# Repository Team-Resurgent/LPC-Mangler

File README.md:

# LPC Mangler
 
A WIP/Concept Mod for original xbox. Designed by Members from Team Resurgent.
It intercepts the LPC commands between the chipset and an LPC flash chip, rewriting the command and address bits so you can use larger, later chips that don't normally reside at the same addresses as typical LPC flash chips used in simpler mods like the Aladdin , and does so while adding as few extra clock cycles as possible to the transaction

Would love for the community to contribute & complete the design

Currently supports upto 4MB Flashes. Also has ability for serial output etc.

Requires Lframe to be implemented to work with higher rev xbox possibly.

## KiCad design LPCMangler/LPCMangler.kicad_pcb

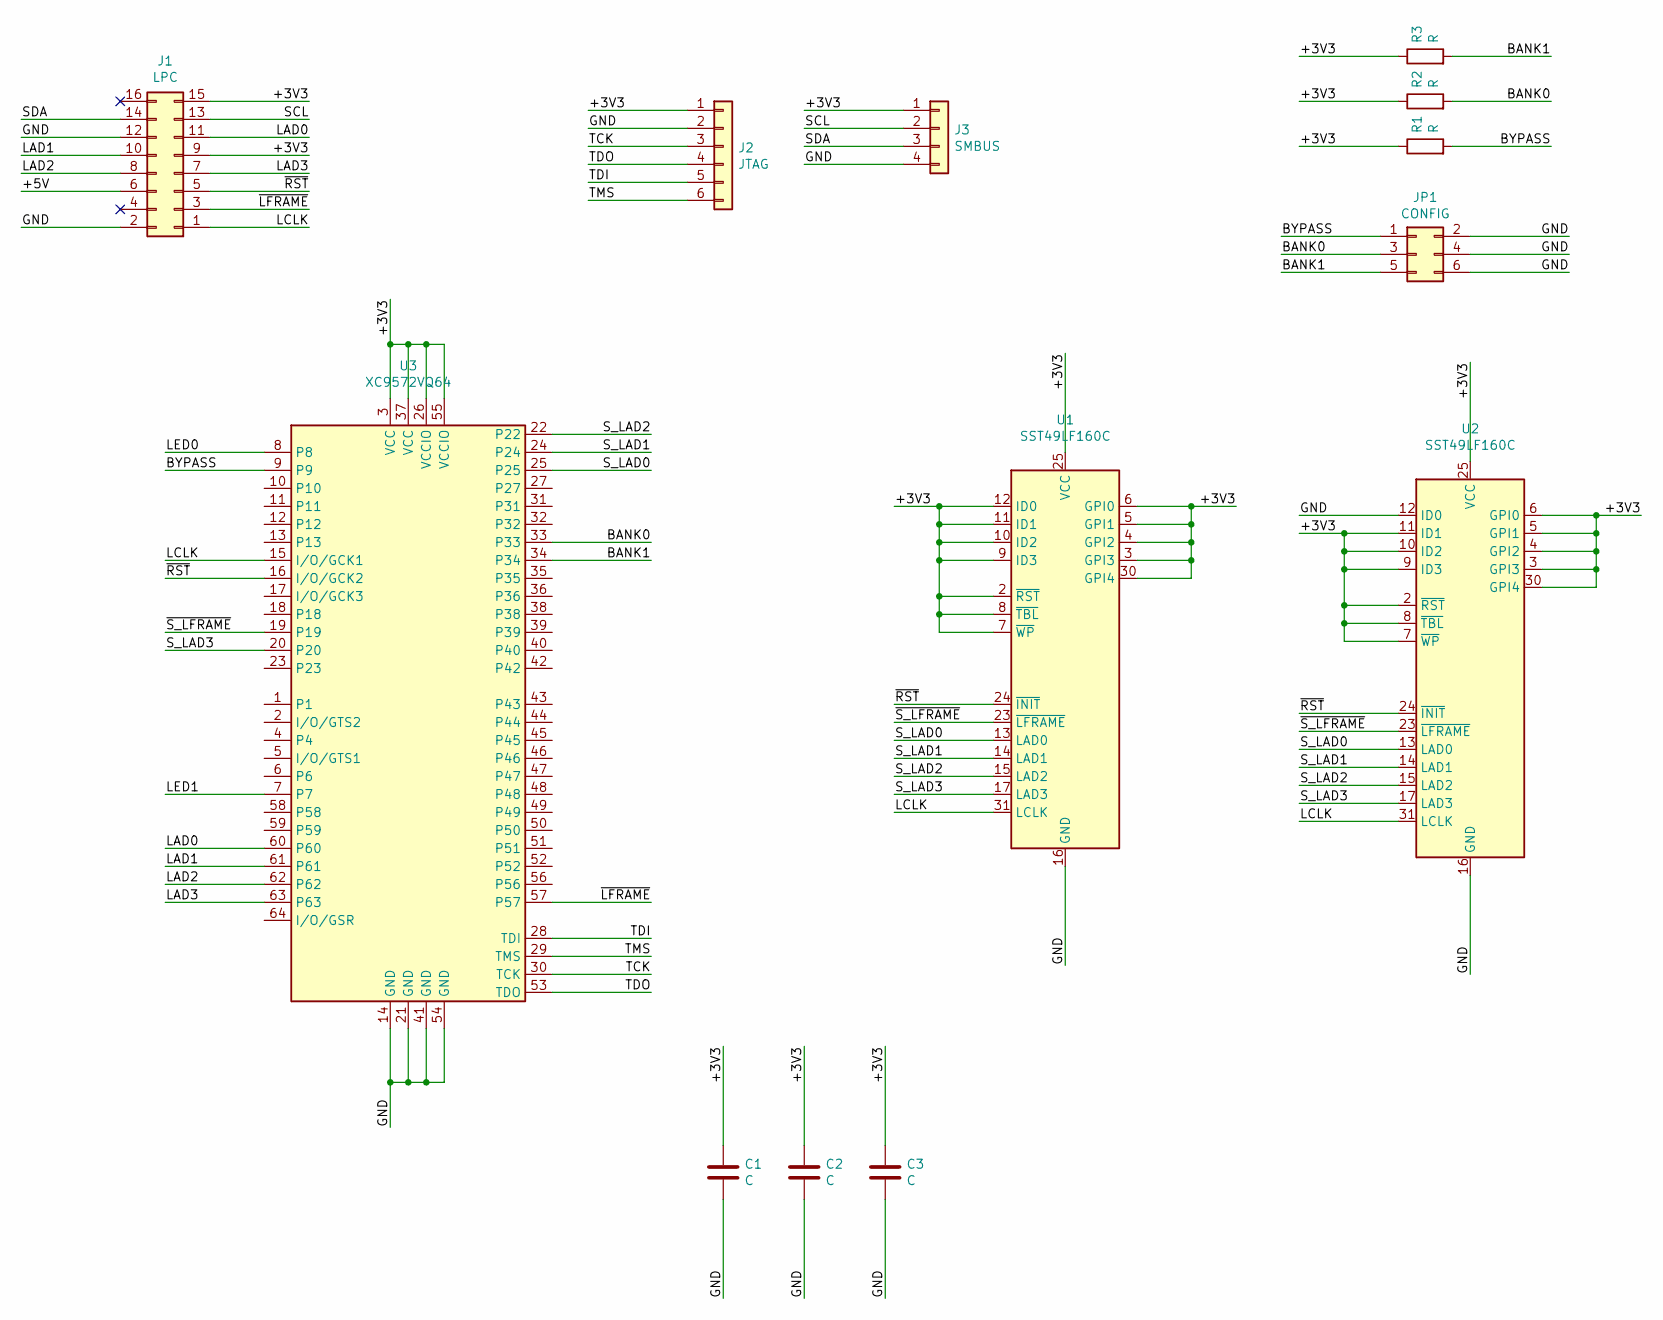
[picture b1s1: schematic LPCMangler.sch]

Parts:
C1, C2, C3: C; C_0603_1608Metric_Pad1.08x0.95mm_HandSolder
J1: LPC; PinSocket_2x08_P2.54mm_Vertical
J2: JTAG; PinHeader_1x06_P2.54mm_Vertical
J3: SMBUS; PinHeader_1x04_P2.54mm_Vertical
JP1: CONFIG; PinHeader_2x03_P2.54mm_Vertical
R1, R2, R3: R; R_0603_1608Metric_Pad0.98x0.95mm_HandSolder
U1, U2: SST49LF160C; PLCC-32_THT-Socket
U3: XC9572VQ64; TQFP-64_10x10mm_P0.5mm

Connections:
/+3V3: C1.1, C2.1, C3.1, J1.9, J1.15, J2.1, J3.1, R1.1, R2.1, R3.1, U1.2 (~RST), U1.3 (GPI3), U1.4 (GPI2), U1.5 (GPI1), U1.6 (GPI0), U1.7 (~WP), U1.8 (~TBL), U1.9 (ID3), U1.10 (ID2), U1.11 (ID1), U1.12 (ID0), U1.25 (VCC), U1.30 (GPI4), U2.2 (~RST), U2.3 (GPI3), U2.4 (GPI2), U2.5 (GPI1), U2.6 (GPI0), U2.7 (~WP), U2.8 (~TBL), U2.9 (ID3), U2.10 (ID2), U2.11 (ID1), U2.25 (VCC), U2.30 (GPI4), U3.3 (VCC), U3.26 (VCCIO), U3.37 (VCC), U3.55 (VCCIO)
/+5V: J1.6
/BANK0: JP1.3, R2.2, U3.33
/BANK1: JP1.5, R3.2, U3.34
/BYPASS: JP1.1, R1.2, U3.9
/GND: C1.2, C2.2, C3.2, J1.2, J1.12, J2.2, J3.4, JP1.2, JP1.4, JP1.6, U1.16 (GND), U2.12 (ID0), U2.16 (GND), U3.14 (GND), U3.21 (GND), U3.41 (GND), U3.54 (GND)
/LAD0: J1.11, U3.60
/LAD1: J1.10, U3.61
/LAD2: J1.8, U3.62
/LAD3: J1.7, U3.63
/LCLK: J1.1, U1.31 (LCLK), U2.31 (LCLK), U3.15 (I/O/GCK1)
/LED0: U3.8
/LED1: U3.7
/SCL: J1.13, J3.2
/SDA: J1.14, J3.3
/S_LAD0: U1.13 (LAD0), U2.13 (LAD0), U3.25
/S_LAD1: U1.14 (LAD1), U2.14 (LAD1), U3.24
/S_LAD2: U1.15 (LAD2), U2.15 (LAD2), U3.22
/S_LAD3: U1.17 (LAD3), U2.17 (LAD3), U3.20
/TCK: J2.3, U3.30 (TCK)
/TDI: J2.5, U3.28 (TDI)
/TDO: J2.4, U3.53 (TDO)
/TMS: J2.6, U3.29 (TMS)
/~LFRAME: J1.3, U3.57
/~RST: J1.5, U1.24 (~INIT), U2.24 (~INIT), U3.16 (I/O/GCK2)
/~S_LFRAME: U1.23 (~LFRAME), U2.23 (~LFRAME), U3.19

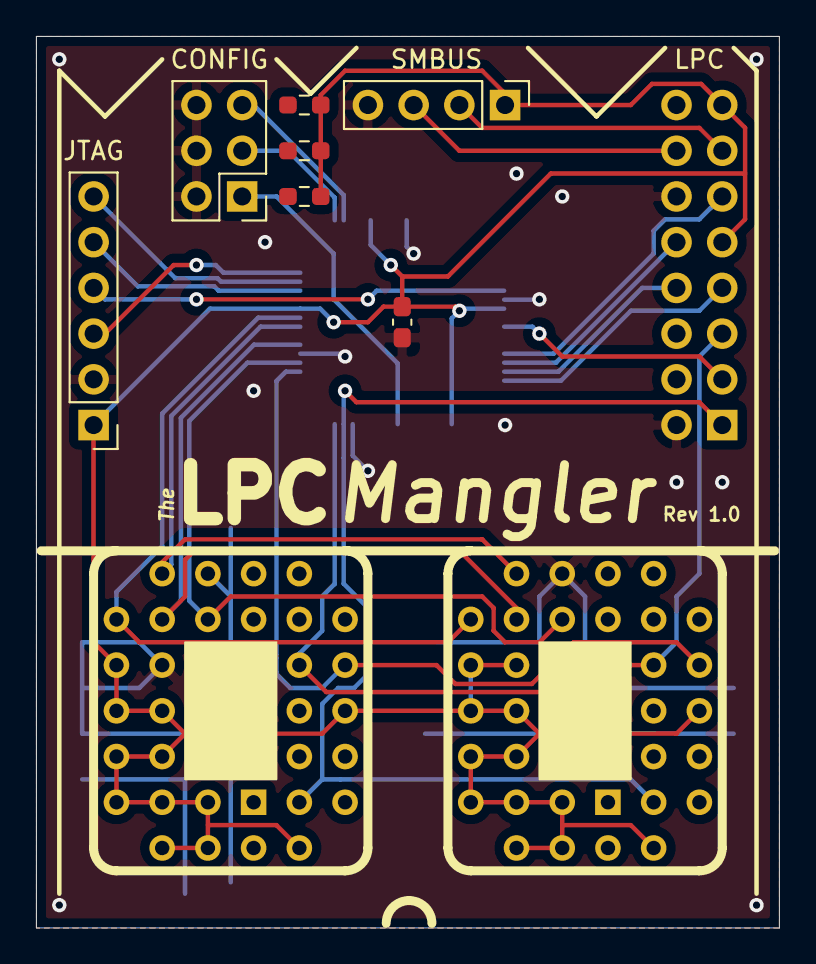
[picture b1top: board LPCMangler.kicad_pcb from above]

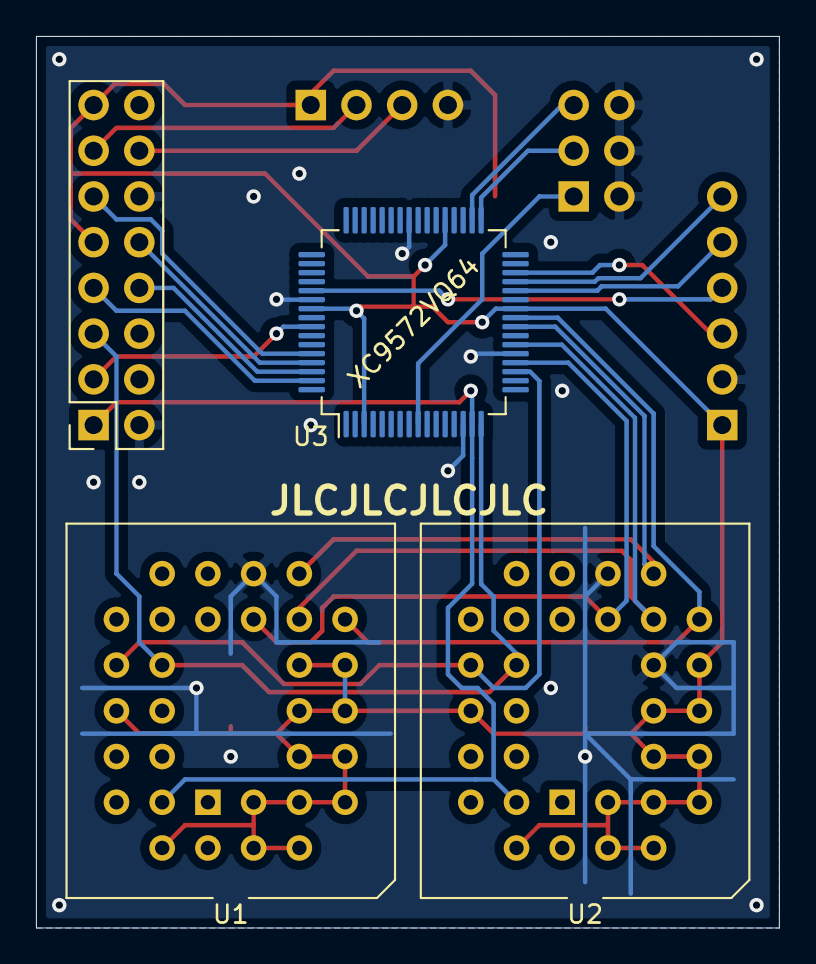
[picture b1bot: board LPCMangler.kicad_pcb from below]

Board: 2 copper layers, 41.3 x 49.5 mm, 13 parts (4 on the bottom side), 23 nets.

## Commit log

2023-08-07 Initial release
2023-08-07 Added Pics
